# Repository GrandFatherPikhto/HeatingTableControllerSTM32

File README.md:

# Reflow Oven & Heating Table Controller (STM32F103C8T6)

*Читать на русском: [README_ru.md](README_ru.md)*

Hardware design (KiCad schematics and PCB layout) for a dual-channel controller designed for reflow ovens, hot plates, infrared/convection soldering stations, and PCB drying chambers.

The controller is based on the **STM32F103C8T6** microcontroller and supports two independent heating zones (e.g., top and bottom heaters) along with two K-type thermocouples via **MAX6675** cold-junction compensated converters.

---

## Key Features & Hardware Architecture

* **Microcontroller:** STM32F103C8T6 (LQFP-48) with an external 8 MHz HSE crystal and a 32.768 kHz LSE crystal for RTC.
* **Dual-Channel Temperature Sensing:** Supports two K-type thermocouple modules based on **MAX6675** sharing a common SPI bus (`PA5` SCK, `PA6` MISO) with dedicated chip-select lines (`PA3`, `PA4`).
* **Isolated Sensor Power Rails:** To minimize noise and cross-talk between thermocouple readings, the MCU and each MAX6675 module are powered by separate **AMS1117-3.3** linear voltage regulators (`U1`, `U2`, `U3`).
* **Dual-Channel Heater Control:** Control outputs (`PB8` and `PB9`) are buffered by **74HC14D** (`U6`): two Schmitt-trigger inverters in series per channel, so the output follows the MCU pin (active high). The 10 kΩ pull-downs `R14`/`R15` sit on the buffer **outputs** and hold the lines low only while the controller is unpowered or disconnected. The outputs drive the triac power board ([`../Power`](../Power)) or an SSR. See note 4 about the MCU reset state.
* **User Interface:**
  * **LCD1602** character display interface over I2C (`PB6` SCL, `PB7` SDA) through an on-board bidirectional 3.3 V ↔ 5 V level shifter (**BSS138** `Q2`/`Q3`, 4.7 kΩ pull-ups on both sides).
  * Rotary encoder with push-button (`PA0`, `PA1`, `PA2`) through on-board 3.3 V ↔ 5 V level shifters (**BSS138** `Q4`–`Q6`, 4.7 kΩ pull-ups on both sides) for menu navigation and thermal profile configuration.
  * External status LED outputs for both heater channels and buzzer indication buffered via **74HC14D** (`U5`).
  * Piezo/magnetic buzzer driven by an `MMBT3904` NPN transistor (`PB12`).
* **Protection & Debugging:**
  * Resettable PTC fuse `MF-MSMF075-2` (0.75 A) and input bulk/bypass filtering on the +5 V power rail.
  * Dedicated **SWD** and **USART** (`PA9` TX, `PA10` RX) headers for flashing and debugging.

---

## Repository Structure

* `ControllerSTM32F103C8T6.kicad_pro` — KiCad project file.
* `ControllerSTM32F103C8T6.kicad_sch` — Root schematic sheet.
* `power.kicad_sch` — Power supply and 3.3 V LDO regulators sheet.
* `mcu.kicad_sch` — STM32F103C8T6, Schmitt-trigger buffers, I2C and encoder level shifters, and connectors sheet.
* `ControllerSTM32F103C8T6.kicad_pcb` — PCB layout (with 4× M3 mounting holes).
* `out/ControllerSTM32F103C8T6_bom.txt` — Bill of Materials (BOM).
* `out/ControllerSTM32F103C8T6_net.txt` — Simplified netlist.

---

## Connector Pinouts

### J1 — Power Input (`+5V In`, JST-XH 2-pin)

| Pin | Signal | Description |
| :---: | :--- | :--- |
| 1 | `+5P` | +5 V power input (before fuse F1) |
| 2 | `GND` | Ground |

### J10 — Heater Control Outputs (`Signal Out`, JST-XH 4-pin)

| Pin | Signal | MCU Pin (via U6) | Description |
| :---: | :--- | :--- | :--- |
| 1 | `GND` | — | Channel 1 ground |
| 2 | `HEATER_OUT_01` | `PB8` (pin 45) | Heater 1 control signal (3.3 V logic, active high) |
| 3 | `GND` | — | Channel 2 ground |
| 4 | `HEATER_OUT_02` | `PB9` (pin 46) | Heater 2 control signal (3.3 V logic, active high) |

### J7 / J8 — Thermocouple Sensors (`MAX6675_01` / `MAX6675_02`, JST-XH 5-pin)

| Pin | Signal | MCU Pin | Description |
| :---: | :--- | :--- | :--- |
| 1 | `+3V3_MAX6675_01 / 02` | — | Dedicated +3.3 V supply |
| 2 | `GND` | — | Ground |
| 3 | `MAX_SCK` | `PA5` (pin 15) | SPI clock (SCK) |
| 4 | `MAX_CS_01 / 02` | `PA3` (pin 13) / `PA4` (pin 14) | Chip Select |
| 5 | `MAX_MISO` | `PA6` (pin 16) | SPI data from MAX6675 (SO / MISO) |

### J4 — Display (`LCD1602`, JST-XH 4-pin)

| Pin | Signal | MCU Pin | Description |
| :---: | :--- | :--- | :--- |
| 1 | `GND` | — | Ground |
| 2 | `+5V` | — | +5 V display power |
| 3 | `LCD_SDA_5V` | `PB7` (pin 43) via `Q2` | I2C1 data line (SDA), 5 V side of the level shifter |
| 4 | `LCD_SCL_5V` | `PB6` (pin 42) via `Q3` | I2C1 clock line (SCL), 5 V side of the level shifter |

### J6 — Rotary Encoder (`Rotary Encoder`, JST-XH 5-pin)

| Pin | Signal | MCU Pin | Description |
| :---: | :--- | :--- | :--- |
| 1 | `+5V` | — | Encoder module power |
| 2 | `RENC_A_P5V` | `PA0` (pin 10) via `Q4` | Encoder phase A, 5 V side of the level shifter |
| 3 | `RENC_B_P5V` | `PA1` (pin 11) via `Q5` | Encoder phase B, 5 V side of the level shifter |
| 4 | `RENC_BUTTON_P5V` | `PA2` (pin 12) via `Q6` | Encoder push-button, 5 V side of the level shifter |
| 5 | `GND` | — | Ground |

### J9 — External Status LEDs (`Led Out`, JST-XH 5-pin)

| Pin | Signal | MCU Pin (via U5) | Description |
| :---: | :--- | :--- | :--- |
| 1 | `HEATER_LED_OUT_01` | `PB10` (pin 21) | Heater 1 LED anode (via 330 Ω resistor) |
| 2 | `GND` | — | Heater 1 LED cathode |
| 3 | `HEATER_LED_OUT_02` | `PB11` (pin 22) | Heater 2 LED anode (via 330 Ω resistor) |
| 4 | `GND` | — | Heater 2 LED cathode |
| 5 | `BUZZER_LED_OUT` | `PB13` (pin 26) | Buzzer indicator LED anode (via 330 Ω resistor) |

### J3 — UART Interface (`USART`, JST-XH 4-pin)

| Pin | Signal | MCU Pin | Description |
| :---: | :--- | :--- | :--- |
| 1 | `GND` | — | Ground |
| 2 | `TX` | `PA9` (pin 30) | USART1 transmit |
| 3 | `GND` | — | Ground |
| 4 | `RX` | `PA10` (pin 31) | USART1 receive |

### J5 — Debug Interface (`SWD`, PinHeader 1x5, 2.54 mm pitch)

| Pin | Signal | MCU Pin | Description |
| :---: | :--- | :--- | :--- |
| 1 | `+3V3_STM32` | — | +3.3 V reference voltage |
| 2 | `SWDIO` | `PA13` (pin 34) | SWD data I/O |
| 3 | `SWCLK` | `PA14` (pin 37) | SWD clock |
| 4 | `NRST` | `NRST` (pin 7) | Hardware reset |
| 5 | `GND` | — | Ground |

---

## Assembly & Hardware Notes

1. **I2C (`J4`) & Rotary Encoder (`J6`) Logic Levels:**
   * `J4` is on the 5 V side of the on-board level shifter (`Q2`/`Q3`), so a standard PCF8574 I2C backpack for LCD1602 can be connected as is. Its own pull-ups to `+5V` simply add in parallel to `R6`/`R16` (≈ 2.3 kΩ with 4.7 kΩ on the backpack — fine for 100 kHz).
   * Pins `PA0`–`PA2` are **not** 5V-tolerant, so `J6` is also on the 5 V side of on-board level shifters (`Q4`–`Q6`). A 5 V rotary encoder breakout with its own pull-ups can be connected as is; the board already pulls each line up on both sides (4.7 kΩ).
2. **32.768 kHz Crystal (`Y2`):** Load capacitors `C19` and `C31` are `6.8 pF`, suitable for crystals rated at `CL = 6–7 pF`. If using a standard `CL = 12.5 pF` crystal, replace `C19` and `C31` with `15–18 pF` C0G/NP0 capacitors.
3. **Flashing Firmware:** Close jumper `J2 (Boot)` to pull `BOOT0` high when flashing via the built-in UART bootloader (`J3`). Keep `J2` open during normal operation.
4. **Heater outputs during MCU reset (current revision):** while the STM32 is in reset, being flashed, or halted before its GPIO is configured, `PB8`/`PB9` are floating inputs. The inputs of `U6` then float too, and `U6` actively drives `J10` to an undefined level — `R14`/`R15` (and the pull-downs on the power board) cannot override it, so a heater may switch on. Fix for the next revision: add 10–100 kΩ pull-downs from `HEATER_01`/`HEATER_02` to `GND` at the `U6` inputs (pins 3 and 1). Until then, keep the mains off while flashing or debugging.

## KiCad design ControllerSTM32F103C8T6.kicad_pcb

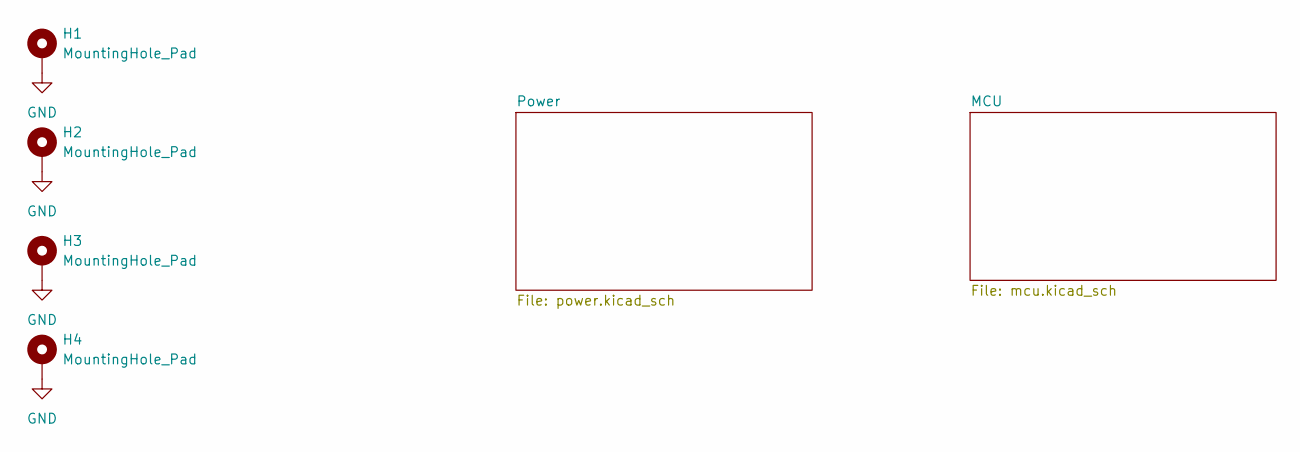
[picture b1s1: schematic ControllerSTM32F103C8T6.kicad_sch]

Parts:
H1, H2, H3, H4: MountingHole_Pad; MountingHole_3.2mm_M3_DIN965_Pad

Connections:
GND: H1.1 (1_1), H2.1 (1_1), H3.1 (1_1), H4.1 (1_1); also elsewhere on the board

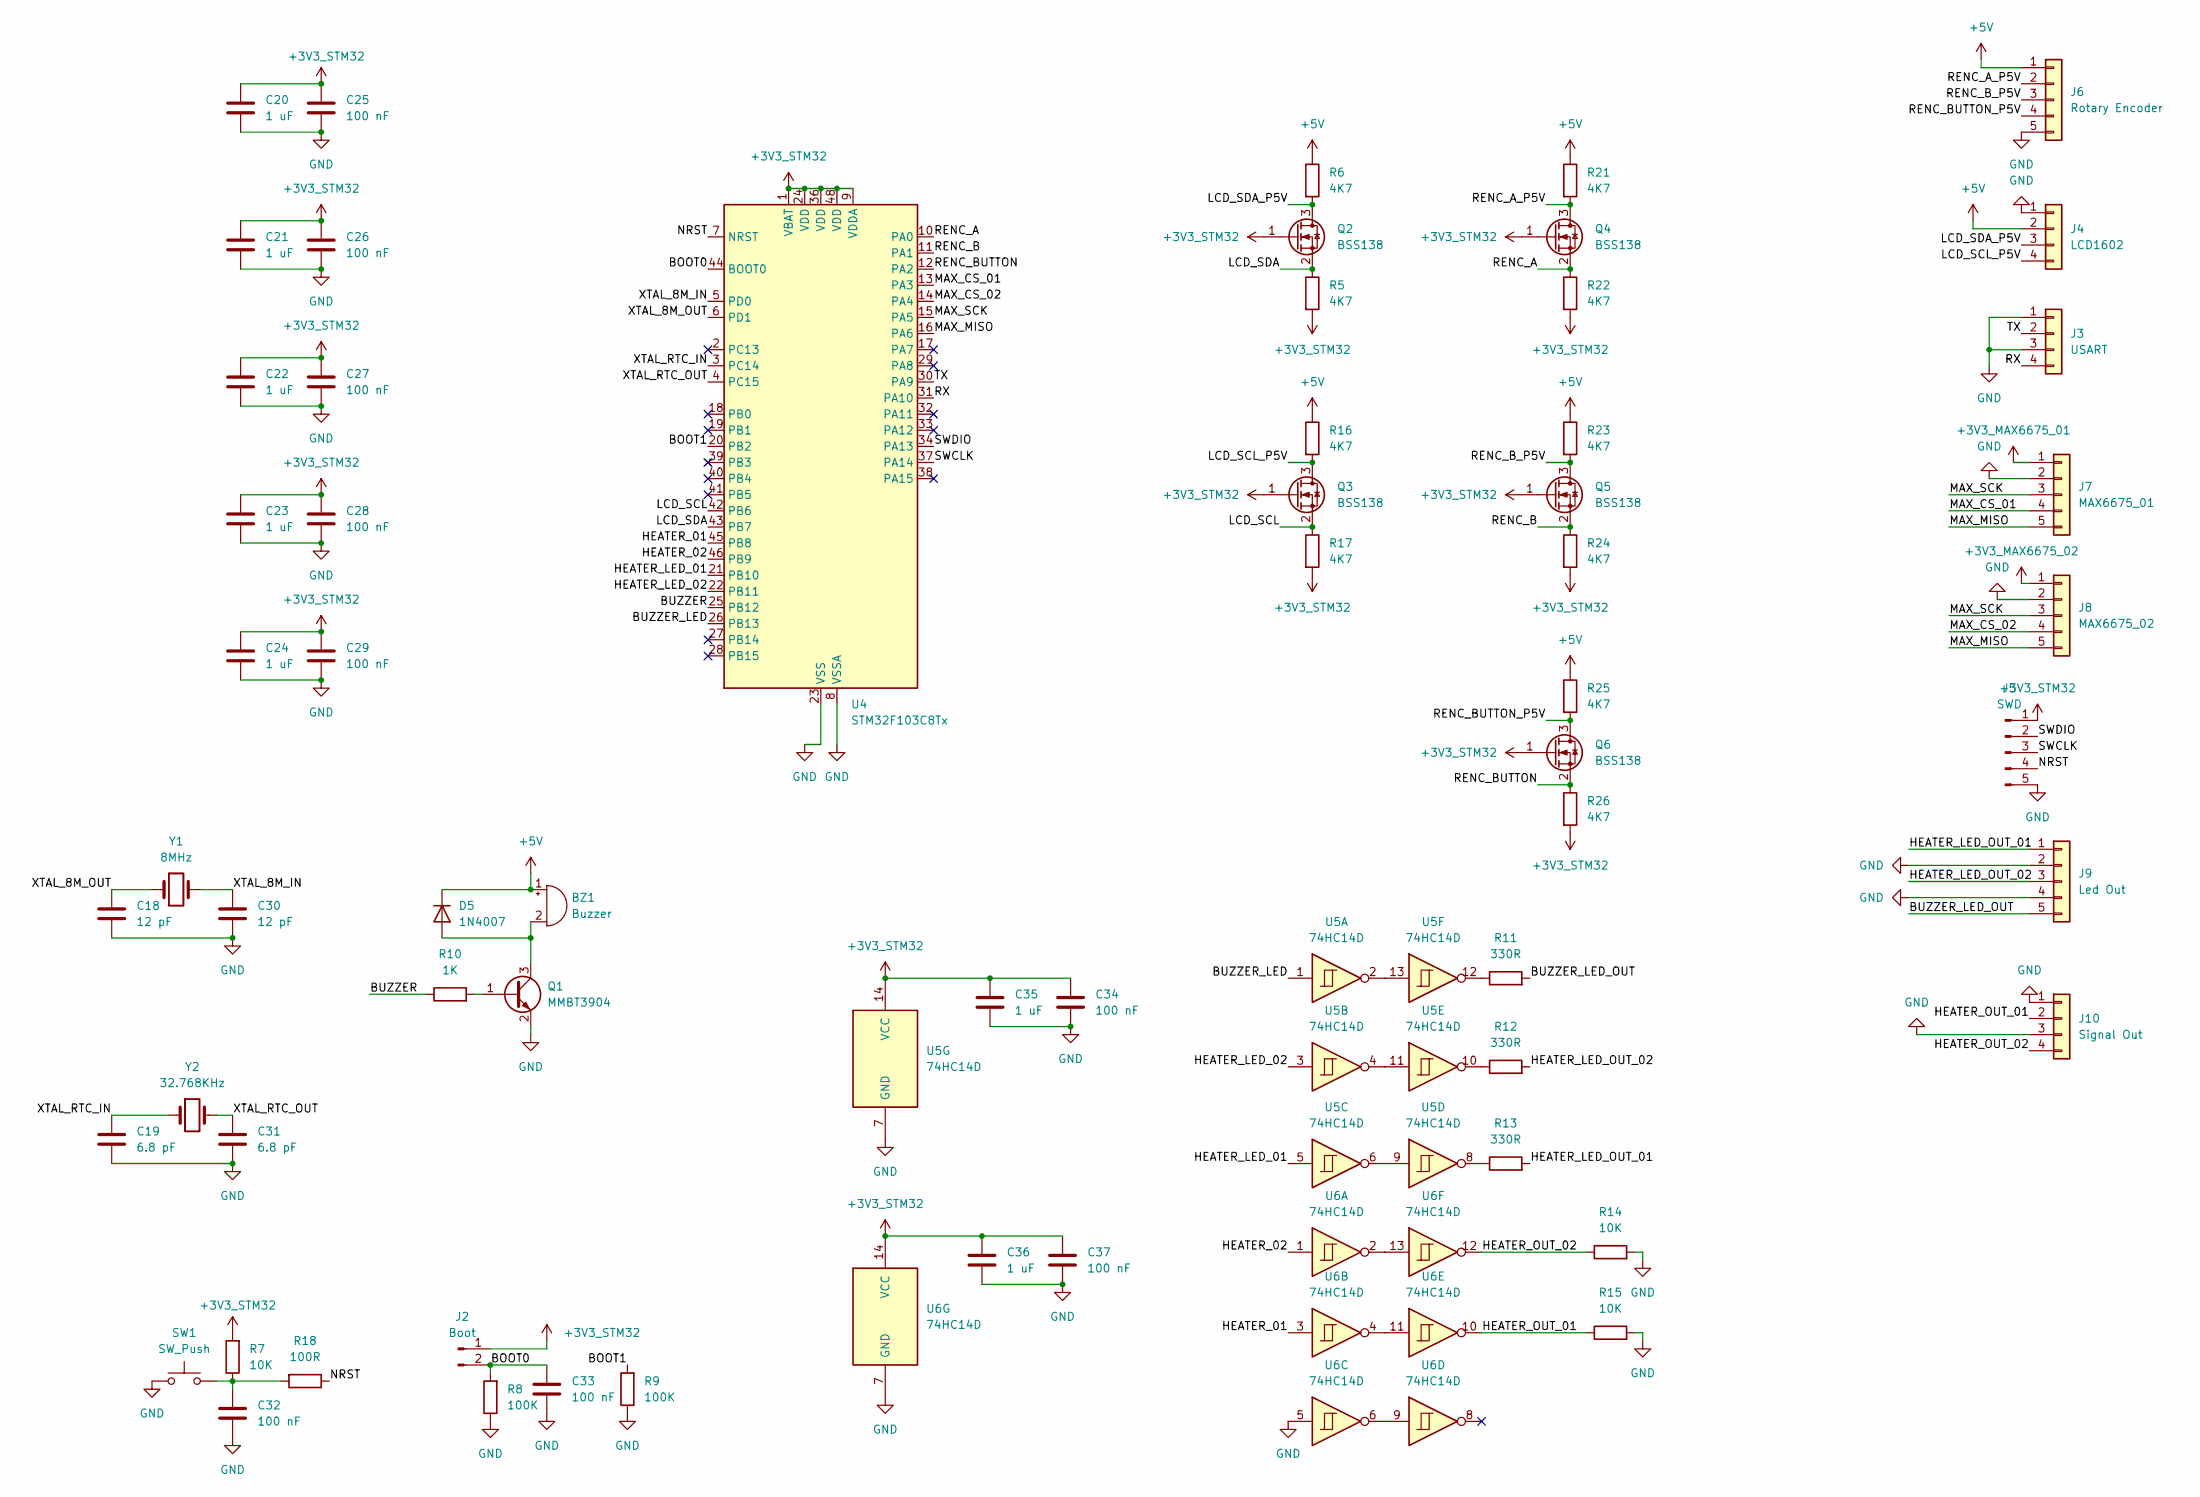
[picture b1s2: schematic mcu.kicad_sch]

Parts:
BZ1: Buzzer; Buzzer_12x9.5RM7.6
C18, C30: 12 pF; C_0402_1005Metric_Pad0.74x0.62mm_HandSolder
C19, C31: 6.8 pF; C_0402_1005Metric_Pad0.74x0.62mm_HandSolder
C20, C21, C22, C23, C24, C35, C36: 1 uF; C_0603_1608Metric_Pad1.08x0.95mm_HandSolder
C25, C26, C27, C28, C29, C32: 100 nF; C_0603_1608Metric_Pad1.08x0.95mm_HandSolder
C33, C34, C37: 100 nF; C_0402_1005Metric_Pad0.74x0.62mm_HandSolder
D5: 1N4007; D_SOD-123
J2: Boot; PinHeader_1x02_P2.54mm_Vertical
J3: USART; JST_XH_B4B-XH-A_1x04_P2.50mm_Vertical
J4: LCD1602; JST_XH_B4B-XH-A_1x04_P2.50mm_Vertical
J5: SWD; PinHeader_1x05_P2.54mm_Vertical
J6: Rotary Encoder; JST_XH_B5B-XH-A_1x05_P2.50mm_Vertical
J7: MAX6675_01; JST_XH_B5B-XH-A_1x05_P2.50mm_Vertical
J8: MAX6675_02; JST_XH_B5B-XH-A_1x05_P2.50mm_Vertical
J9: Led Out; JST_XH_B5B-XH-A_1x05_P2.50mm_Vertical
J10: Signal Out; JST_XH_B4B-XH-A_1x04_P2.50mm_Vertical
Q1: MMBT3904; SOT-23
Q2, Q3, Q4, Q5, Q6: BSS138; SOT-23
R5, R6, R16, R17, R21, R22, R23, R24, R25, R26: 4K7; R_0402_1005Metric_Pad0.72x0.64mm_HandSolder
R7: 10K; R_0603_1608Metric_Pad0.98x0.95mm_HandSolder
R8, R9: 100K; R_0402_1005Metric_Pad0.72x0.64mm_HandSolder
R10: 1K; R_0603_1608Metric_Pad0.98x0.95mm_HandSolder
R11, R12, R13: 330R; R_0603_1608Metric_Pad0.98x0.95mm_HandSolder
R14, R15: 10K; R_0402_1005Metric_Pad0.72x0.64mm_HandSolder
R18: 100R; R_0603_1608Metric_Pad0.98x0.95mm_HandSolder
SW1: SW_Push; SW_PUSH_6mm
U4: STM32F103C8Tx; LQFP-48_7x7mm_P0.5mm
U5, U6: 74HC14D; SOIC-14_3.9x8.7mm_P1.27mm
Y1: 8MHz; Crystal_HC49-4H_Vertical
Y2: 32.768KHz; Crystal_C38-LF_D3.0mm_L8.0mm_Vertical

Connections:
+3V3_MAX6675_01: J7.1; also elsewhere on the board
+3V3_MAX6675_02: J8.1; also elsewhere on the board
+3V3_STM32: C20.1, C21.1, C22.1, C23.1, C24.1, C25.1, C26.1, C27.1, C28.1, C29.1, C34.1, C35.1, C36.1, C37.1, J2.1, J5.1, Q2.1 (G), Q3.1 (G), Q4.1 (G), Q5.1 (G), Q6.1 (G), R5.2, R7.2, R17.2, R22.2, R24.2, R26.2, U4.1 (VBAT), U4.9 (VDDA), U4.24 (VDD), U4.36 (VDD), U4.48 (VDD), U5.14 (VCC), U6.14 (VCC); also elsewhere on the board
+5V: BZ1.1 (+), D5.1 (K), J4.2, J6.1, R6.1, R16.1, R21.1, R23.1, R25.1; also elsewhere on the board
/MCU/BOOT0: C33.1, J2.2, R8.2, U4.44 (BOOT0)
/MCU/BOOT1: R9.2, U4.20 (PB2)
/MCU/BUZZER: R10.1, U4.25 (PB12)
/MCU/BUZZER_LED: U4.26 (PB13), U5.1
/MCU/BUZZER_LED_OUT: J9.5, R11.2
/MCU/HEATER_01: U4.45 (PB8), U6.3
/MCU/HEATER_02: U4.46 (PB9), U6.1
/MCU/HEATER_LED_01: U4.21 (PB10), U5.5
/MCU/HEATER_LED_02: U4.22 (PB11), U5.3
/MCU/HEATER_LED_OUT_01: J9.1, R13.2
/MCU/HEATER_LED_OUT_02: J9.3, R12.2
/MCU/HEATER_OUT_01: J10.2, R15.1, U6.10
/MCU/HEATER_OUT_02: J10.4, R14.1, U6.12
/MCU/LCD_SCL: Q3.2 (S), R17.1, U4.42 (PB6)
/MCU/LCD_SCL_P5V: J4.4, Q3.3 (D), R16.2
/MCU/LCD_SDA: Q2.2 (S), R5.1, U4.43 (PB7)
/MCU/LCD_SDA_P5V: J4.3, Q2.3 (D), R6.2
/MCU/MAX_CS_01: J7.4, U4.13 (PA3)
/MCU/MAX_CS_02: J8.4, U4.14 (PA4)
/MCU/MAX_MISO: J7.5, J8.5, U4.16 (PA6)
/MCU/MAX_SCK: J7.3, J8.3, U4.15 (PA5)
/MCU/NRST: J5.4, R18.1, U4.7 (NRST)
/MCU/RENC_A: Q4.2 (S), R22.1, U4.10 (PA0)
/MCU/RENC_A_P5V: J6.2, Q4.3 (D), R21.2
/MCU/RENC_B: Q5.2 (S), R24.1, U4.11 (PA1)
/MCU/RENC_BUTTON: Q6.2 (S), R26.1, U4.12 (PA2)
/MCU/RENC_BUTTON_P5V: J6.4, Q6.3 (D), R25.2
/MCU/RENC_B_P5V: J6.3, Q5.3 (D), R23.2
/MCU/RX: J3.4, U4.31 (PA10)
/MCU/SWCLK: J5.3, U4.37 (PA14)
/MCU/SWDIO: J5.2, U4.34 (PA13)
/MCU/TX: J3.2, U4.30 (PA9)
/MCU/XTAL_8M_IN: C30.1, U4.5 (PD0), Y1.2
/MCU/XTAL_8M_OUT: C18.1, U4.6 (PD1), Y1.1
/MCU/XTAL_RTC_IN: C19.1, U4.3 (PC14), Y2.1
/MCU/XTAL_RTC_OUT: C31.1, U4.4 (PC15), Y2.2
GND: C18.2, C19.2, C20.2, C21.2, C22.2, C23.2, C24.2, C25.2, C26.2, C27.2, C28.2, C29.2, C30.2, C31.2, C32.2, C33.2, C34.2, C35.2, C36.2, C37.2, J3.1, J3.3, J4.1, J5.5, J6.5, J7.2, J8.2, J9.2, J9.4, J10.1, J10.3, Q1.2 (E), R8.1, R9.1, R14.2, R15.2, SW1.1, U4.8 (VSSA), U4.23 (VSS), U4.35 (VSS), U4.47 (VSS), U5.7 (GND), U6.5, U6.7 (GND); also elsewhere on the board
unnamed: BZ1.2 (-), D5.2 (A), Q1.3 (C)
unnamed: C32.1, R7.1, R18.2, SW1.2
unnamed: Q1.1 (B), R10.2
unnamed: R11.1, U5.12
unnamed: R12.1, U5.10
unnamed: R13.1, U5.8
unnamed: U5.6, U5.9
unnamed: U5.4, U5.11
unnamed: U5.2, U5.13
unnamed: U6.6, U6.9
unnamed: U6.4, U6.11
unnamed: U6.2, U6.13

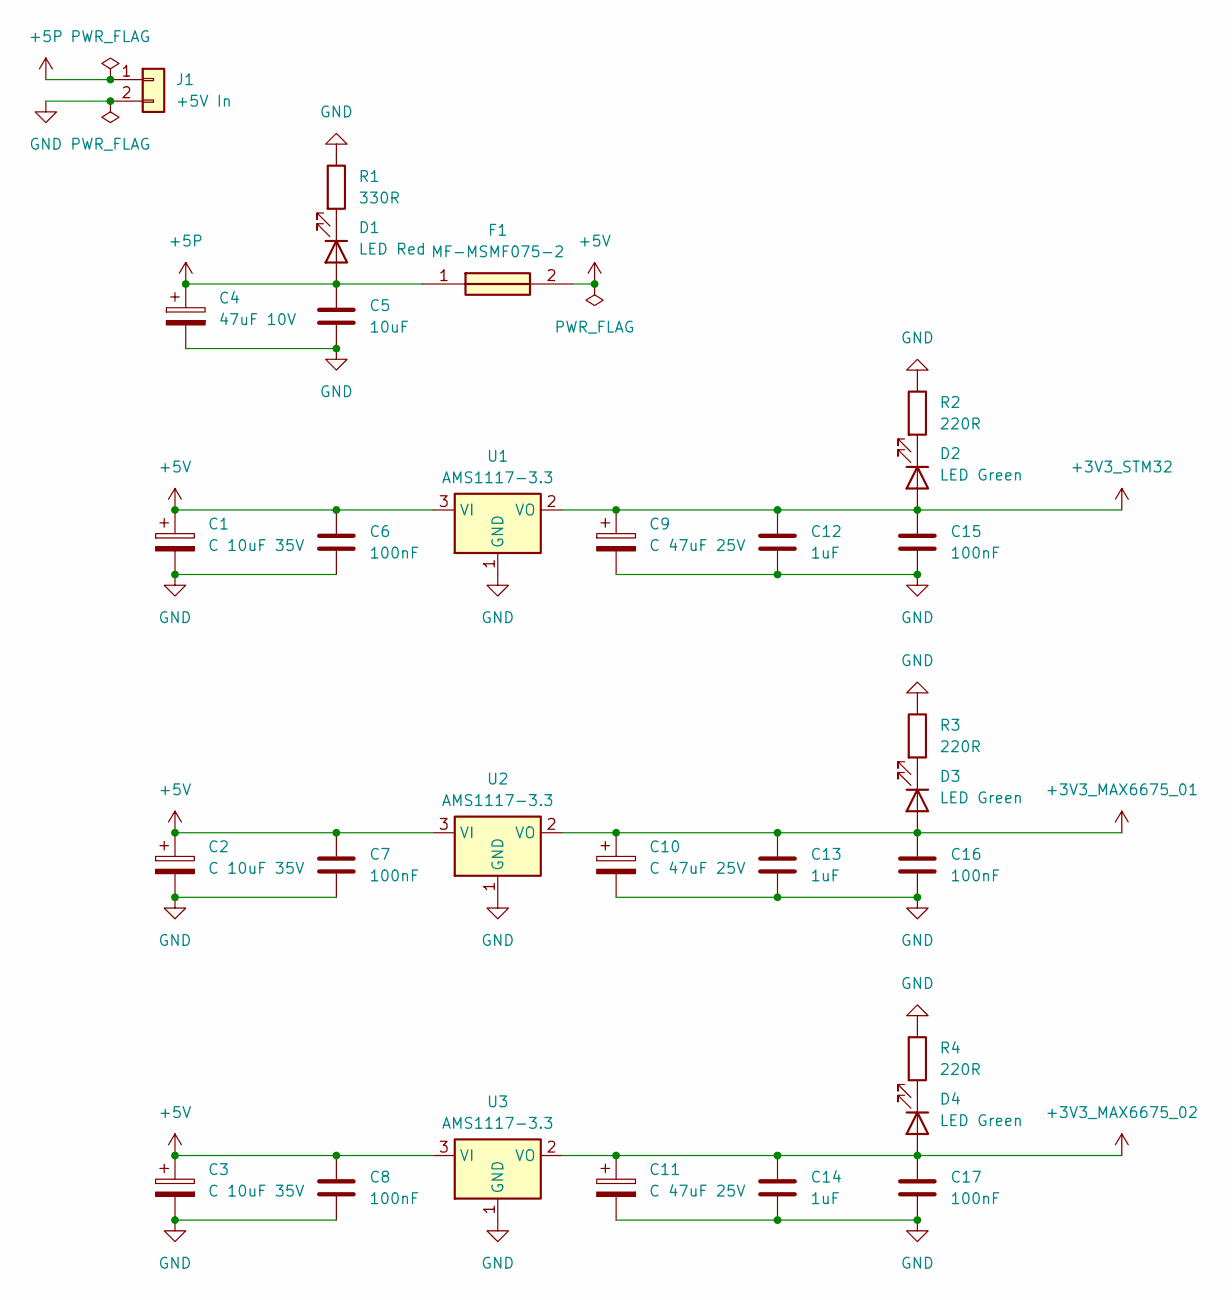
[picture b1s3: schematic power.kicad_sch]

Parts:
C1, C2, C3: C 10uF 35V; CP_EIA-6032-28_Kemet-C
C4: 47uF 10V; CP_Radial_D5.0mm_P2.50mm
C5: 10uF; C_0603_1608Metric_Pad1.08x0.95mm_HandSolder
C6, C7, C8, C15, C16, C17: 100nF; C_0603_1608Metric_Pad1.08x0.95mm_HandSolder
C9, C10, C11: C 47uF 25V; CP_EIA-6032-28_Kemet-C
C12, C13, C14: 1uF; C_0603_1608Metric_Pad1.08x0.95mm_HandSolder
D1: LED Red; LED_0805_2012Metric_Pad1.15x1.40mm_HandSolder
D2, D3, D4: LED Green; LED_0805_2012Metric_Pad1.15x1.40mm_HandSolder
F1: MF-MSMF075-2; FUSC4632X85N; Manufacturer_Part_Number MF-MSMF075-2; Mouser Part Number 652-MF-MSMF075-2
J1: +5V In; JST_XH_B2B-XH-A_1x02_P2.50mm_Vertical
R1: 330R; R_0603_1608Metric_Pad0.98x0.95mm_HandSolder
R2, R3, R4: 220R; R_0603_1608Metric_Pad0.98x0.95mm_HandSolder
U1, U2, U3: AMS1117-3.3; SOT-223-3_TabPin2

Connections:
+3V3_MAX6675_01: C10.1, C13.1, C16.1, D3.2 (A), U2.2 (VO); also elsewhere on the board
+3V3_MAX6675_02: C11.1, C14.1, C17.1, D4.2 (A), U3.2 (VO); also elsewhere on the board
+3V3_STM32: C9.1, C12.1, C15.1, D2.2 (A), U1.2 (VO); also elsewhere on the board
+5P: C4.1, C5.1, D1.2 (A), F1.1, J1.1
+5V: C1.1, C2.1, C3.1, C6.1, C7.1, C8.1, F1.2, U1.3 (VI), U2.3 (VI), U3.3 (VI); also elsewhere on the board
GND: C1.2, C2.2, C3.2, C4.2, C5.2, C6.2, C7.2, C8.2, C9.2, C10.2, C11.2, C12.2, C13.2, C14.2, C15.2, C16.2, C17.2, J1.2, R1.1, R2.1, R3.1, R4.1, U1.1 (GND), U2.1 (GND), U3.1 (GND); also elsewhere on the board
unnamed: D1.1 (K), R1.2
unnamed: D2.1 (K), R2.2
unnamed: D3.1 (K), R3.2
unnamed: D4.1 (K), R4.2

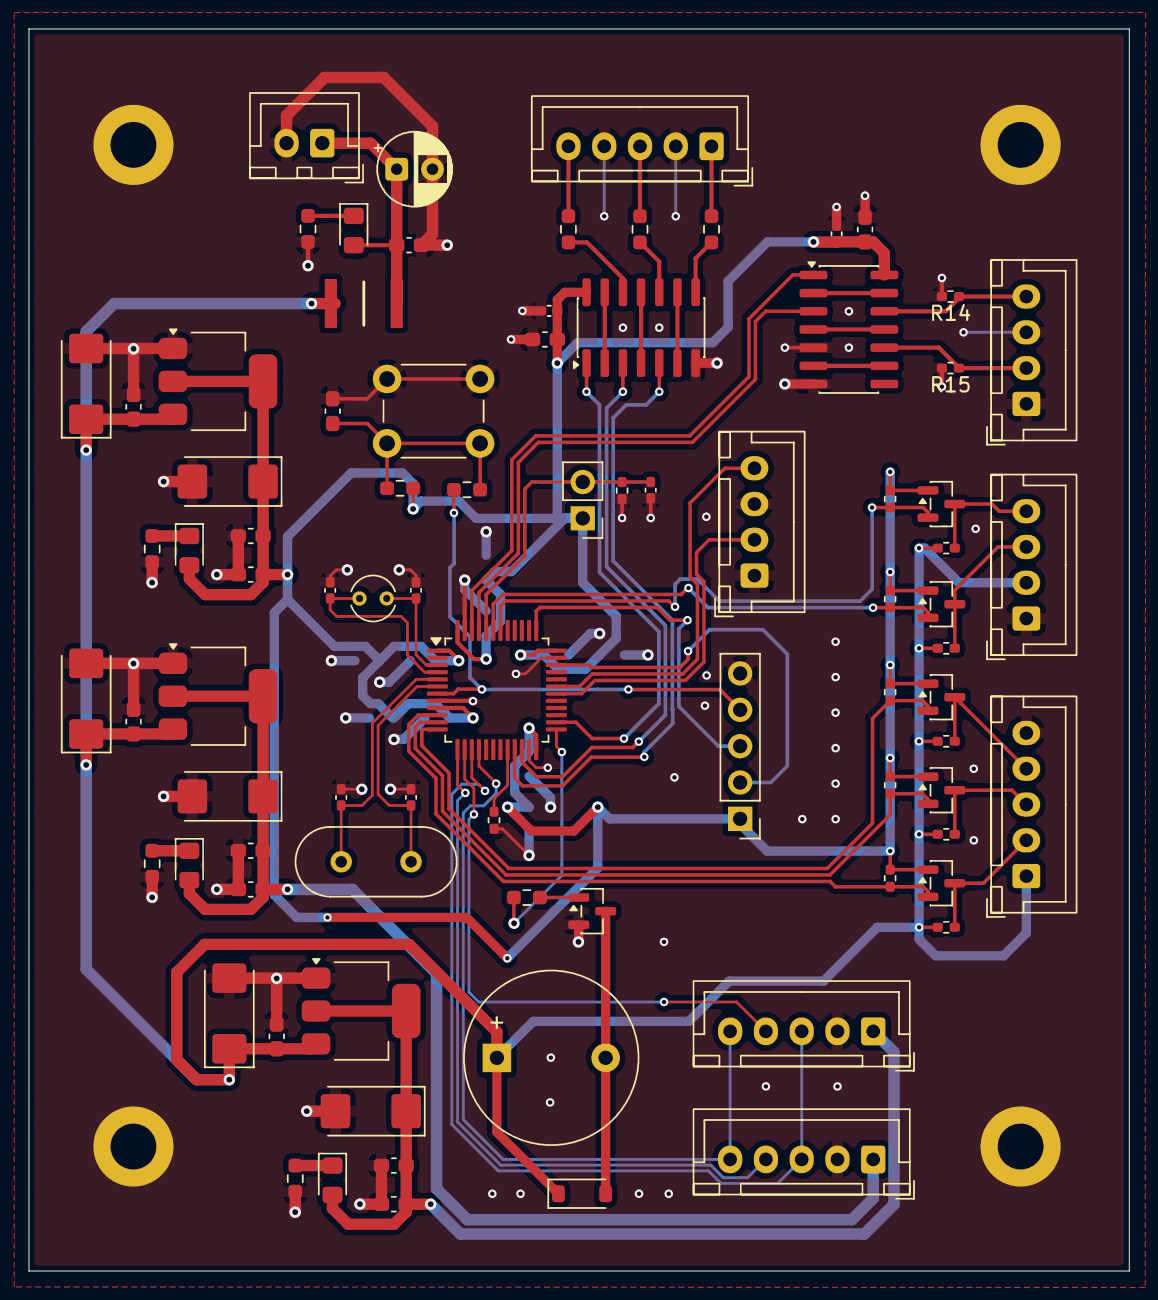
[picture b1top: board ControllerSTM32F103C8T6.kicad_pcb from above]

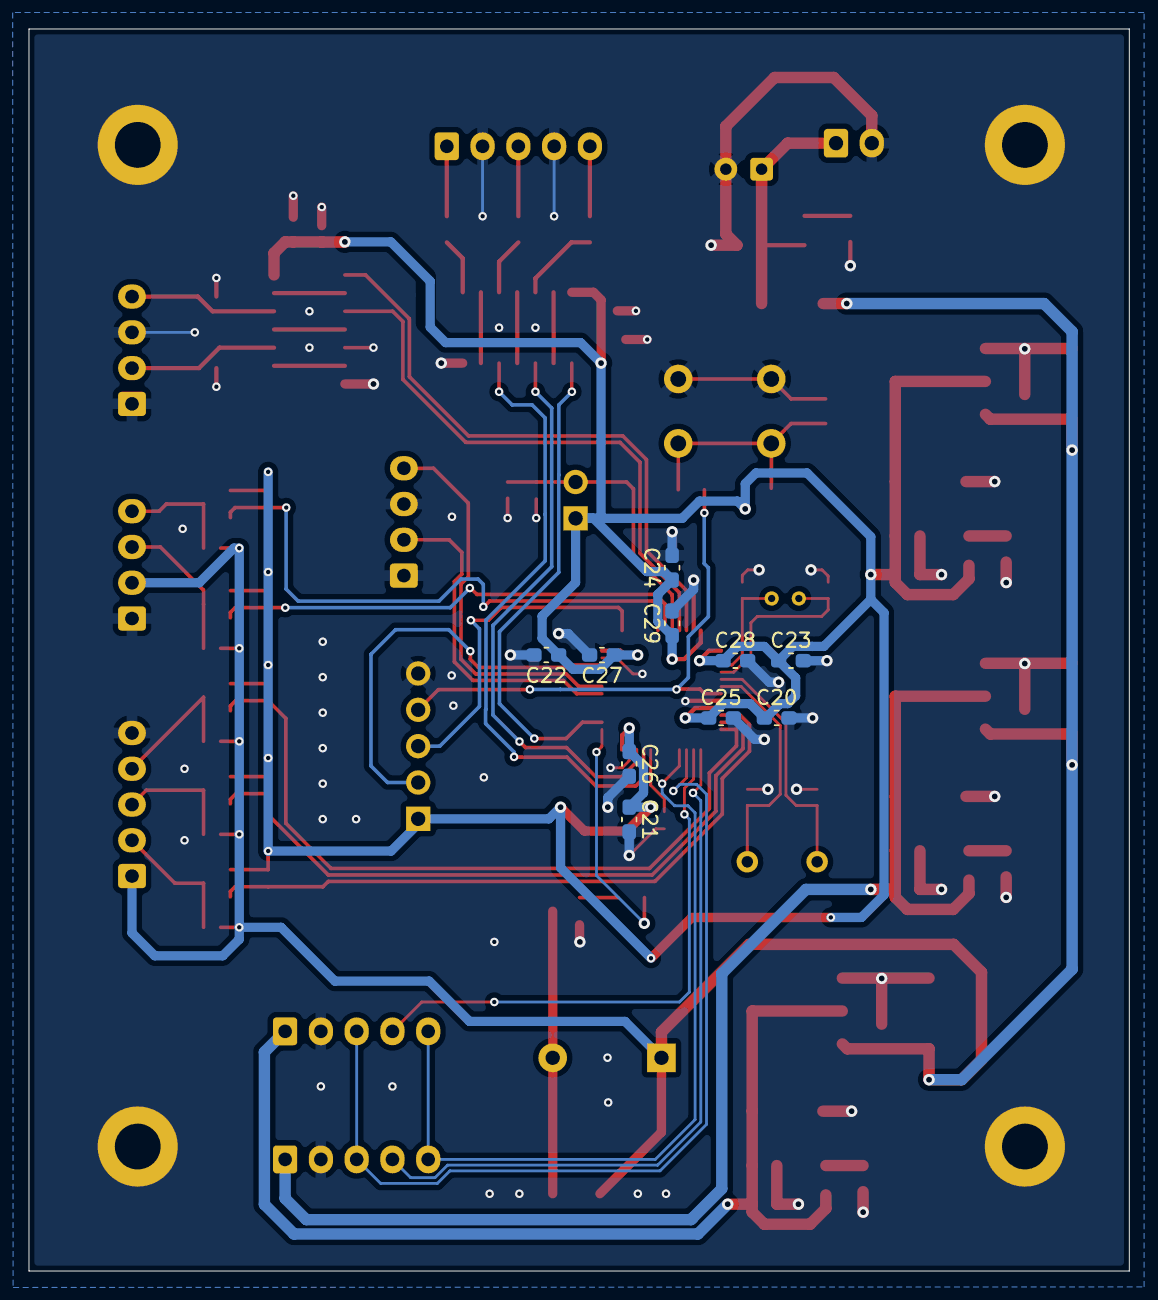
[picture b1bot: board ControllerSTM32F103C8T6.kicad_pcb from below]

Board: 2 copper layers, 76.9 x 86.8 mm, 97 parts (10 on the bottom side), 58 nets.
